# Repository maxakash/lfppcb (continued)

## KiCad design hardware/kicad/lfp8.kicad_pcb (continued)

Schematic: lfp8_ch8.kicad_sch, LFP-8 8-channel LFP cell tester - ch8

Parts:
C801, C802, C806, C808, C811: 10n; C_0603_1608Metric; LCSC C57112
C803, C807: 1u; C_0603_1608Metric; LCSC C15849
C804: 100n; C_0603_1608Metric; LCSC C14663
C805, C810: 47n; C_0603_1608Metric; LCSC C1622
C809: 1n; C_0603_1608Metric; LCSC C1588
D801: SS34; D_SMA; MPN SS34; LCSC C8678
D802, D803, D804, D805, D807, D808, D809, D810: BAT54WS; D_SOD-323; MPN BAT54WS; LCSC C7502694
D806: Green; LED_0805_2012Metric; MPN 0805 green; LCSC C2297
F801: PTC 2A; Fuse_1812_4532Metric; MPN 1812L200/30GR; LCSC C18198342
J801: XH-6P; JST_XH_B6B-XH-A_1x06_P2.50mm_Vertical; MPN JST B6B-XH-A (or clone); JLC Hand
Q801: AO3401A; SOT-23; MPN AO3401A; LCSC C15127
Q802, Q806, Q810, Q811: MMBT3904; SOT-23; MPN MMBT3904; LCSC C20526
Q803: 2N7002; SOT-23; MPN 2N7002; LCSC C8545
Q804, Q805, Q808: AO3400A; SOT-23; MPN AO3400A; LCSC C20917
Q807, Q809: MMBT3906; SOT-23; MPN MMBT3906; LCSC C7420354
R801, R802, R822: 100; R_0603_1608Metric; LCSC C22775
R803, R807, R817, R839: 10k; R_0603_1608Metric; LCSC C25804
R804: 4.7k; R_0603_1608Metric; LCSC C23162
R805, R814, R835, R836, R837, R838, R840: 1k; R_0603_1608Metric; LCSC C21190
R806: 1.2R 2W; R_2512_6332Metric; MPN FRP2512F1R20TS; LCSC C7468247
R808, R809, R810, R811, R812, R818, R823, R832, R844, R848: 100k; R_0603_1608Metric; LCSC C25803
R813: 49.9k; R_0603_1608Metric; LCSC C23184
R815, R834, R841, R851, R852: 47k; R_0603_1608Metric; LCSC C25819
R816: 30k; R_0603_1608Metric; LCSC C22984
R819: 75k; R_0603_1608Metric; LCSC C23242
R820: 36k; R_0603_1608Metric; LCSC C23147
R821, R849: 1M; R_0603_1608Metric; LCSC C22935
R824, R825, R826, R827: 11R 2W; R_2512_6332Metric; MPN FRP2512F11R0TS; LCSC C7468192
R828, R847: 68k; R_0603_1608Metric; LCSC C23231
R829, R842: 33k; R_0603_1608Metric; LCSC C4216
R830: 62k; R_0603_1608Metric; LCSC C23221
R831: 240k; R_0603_1608Metric; LCSC C4197
R833: 150k; R_0603_1608Metric; LCSC C22807
R843: 360k; R_0603_1608Metric; LCSC C23146
R845: 27k; R_0603_1608Metric; LCSC C22967
R846: 200k; R_0603_1608Metric; LCSC C25811
R850: 0.1R 1% 50ppm; R_2512_Kelvin; MPN FRM252WFR100TN; LCSC C7420048
R853: 22k; R_0603_1608Metric; LCSC C31850
R855: 91k; R_0603_1608Metric; LCSC C23265
U801: LM324; SOIC-14_3.9x8.7mm_P1.27mm; MPN LM324DT; LCSC C71035

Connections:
+3V3: R839.1; also elsewhere on the board
+5V: C804.1, C809.2, Q801.2 (S), Q809.2 (E), R803.2, R832.1, R851.1, U801.4 (V+); also elsewhere on the board
/ch8/BNS_8: C802.1, J801.3, R802.1, R836.1, R841.1, R844.1, R847.1
/ch8/BN_8: J801.4, Q805.3 (D), R802.2, R833.1
/ch8/BPF_8: F801.1, J801.1
/ch8/BPS_8: C801.1, J801.2, R801.1, R815.1, R818.1, R828.1, R835.1
/ch8/BP_8: C803.1, F801.2, Q806.2 (E), R801.2, R806.2, R809.1, R824.1, R825.1, R826.1, R827.1, R834.2, R855.2
/ch8/CCN_8: C805.2, R812.2, R813.1, U801.2 (-)
/ch8/CCO_8: D802.1 (K), R814.1, U801.1
/ch8/CCP_8: C810.1, D807.2 (A), R809.2, R810.2, R811.1, U801.3 (+)
/ch8/CCZ_8: C805.1, R814.2
/ch8/CH1_8: D801.2 (A), Q801.3 (D)
/ch8/CH2_8: D801.1 (K), R806.1, R812.1
/ch8/CVO_8: D803.1 (K), R817.1, U801.7
/ch8/CVP_8: C811.1, D808.2 (A), R841.2, R842.2, R843.1, U801.5 (+)
/ch8/CVS_8: C806.2, R815.2, R816.1, U801.6 (-)
/ch8/CVZ_8: C806.1, R817.2
/ch8/DDRV_8: Q803.1 (G), R821.1, R822.1, U801.8
/ch8/DG_8: Q804.1 (G), R822.2, R823.1
/ch8/DLOAD_8: Q804.3 (D), R824.2, R825.2, R826.2, R827.2
/ch8/E2_8: Q802.2 (E), R805.1
/ch8/G1_8: C809.1, Q801.1 (G), Q802.3 (C), R803.1
/ch8/GENB_8: Q810.1 (B), R852.2
/ch8/GEN_8: D804.2 (A), D805.2 (A), D810.1 (K), Q806.3 (C), Q811.3 (C), R832.2, R852.1
/ch8/GISO_8: Q805.1 (G), Q808.1 (G), Q809.3 (C), R853.1
/ch8/GPB_8: Q809.1 (B), Q810.3 (C), R851.2
/ch8/LEDA_8: D806.2 (A), R840.2
/ch8/MIDISO_8: Q805.2 (S), Q808.2 (S), R853.2
/ch8/NBB_8: Q802.1 (B), R804.2
/ch8/NB_8: D802.2 (A), D803.2 (A), D810.2 (A), Q803.3 (D), R804.1, R807.2, R808.1
/ch8/OVO_8: D804.1 (K), R831.1, U801.14
/ch8/OVP_8: R830.2, R831.2, R847.2, R848.1, U801.12 (+)
/ch8/OVS_8: C807.1, D809.2 (A), R828.2, R829.1, U801.13 (-)
/ch8/SHNK_8: R838.1, R850.4
/ch8/SHPK_8: R837.1, R850.3
/ch8/SHP_8: Q808.3 (D), R850.1
/ch8/SNB_8: Q806.1 (B), Q807.2 (E), R833.2, R855.1
/ch8/SNC_8: Q807.3 (C), Q811.1 (B), R849.1
/ch8/SNPB_8: Q807.1 (B), R834.1
/ch8/SUMD_8: R818.2, R819.2, R820.1, R821.2, U801.10 (+)
/ch8/UVN_8: R844.2, R845.2, R846.1, U801.9 (-)
CHGEN_8: D807.1 (K), D808.1 (K), R807.1; also elsewhere on the board
DISEN_8: R819.1; also elsewhere on the board
GND: C801.2, C802.2, C803.2, C804.2, C807.2, C808.2, C810.2, C811.2, D806.1 (K), J801.6, Q803.2 (S), Q804.2 (S), Q810.2 (E), Q811.2 (E), R805.2, R808.2, R811.2, R813.2, R816.2, R820.2, R823.2, R829.2, R843.2, R846.2, R848.2, R849.2, R850.2, U801.11 (V-); also elsewhere on the board
LED_8: R840.1; also elsewhere on the board
MXA_8: R835.2; also elsewhere on the board
MXB_8: R836.2; also elsewhere on the board
MXC_8: R837.2; also elsewhere on the board
MXE_8: R838.2; also elsewhere on the board
NTC_8: C808.1, J801.5, R839.2; also elsewhere on the board
SAFE_EN: D805.1 (K), D809.1 (K); also elsewhere on the board
VREF: R830.1, R842.1, R845.1; also elsewhere on the board
VS: R810.1; also elsewhere on the board

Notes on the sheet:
Cell channel 8: charger, discharger, protection, measurement

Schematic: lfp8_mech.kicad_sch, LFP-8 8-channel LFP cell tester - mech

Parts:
H1, H2, H3, H4: M3; MountingHole_3.2mm_M3; JLC Hand

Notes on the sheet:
Mounting holes

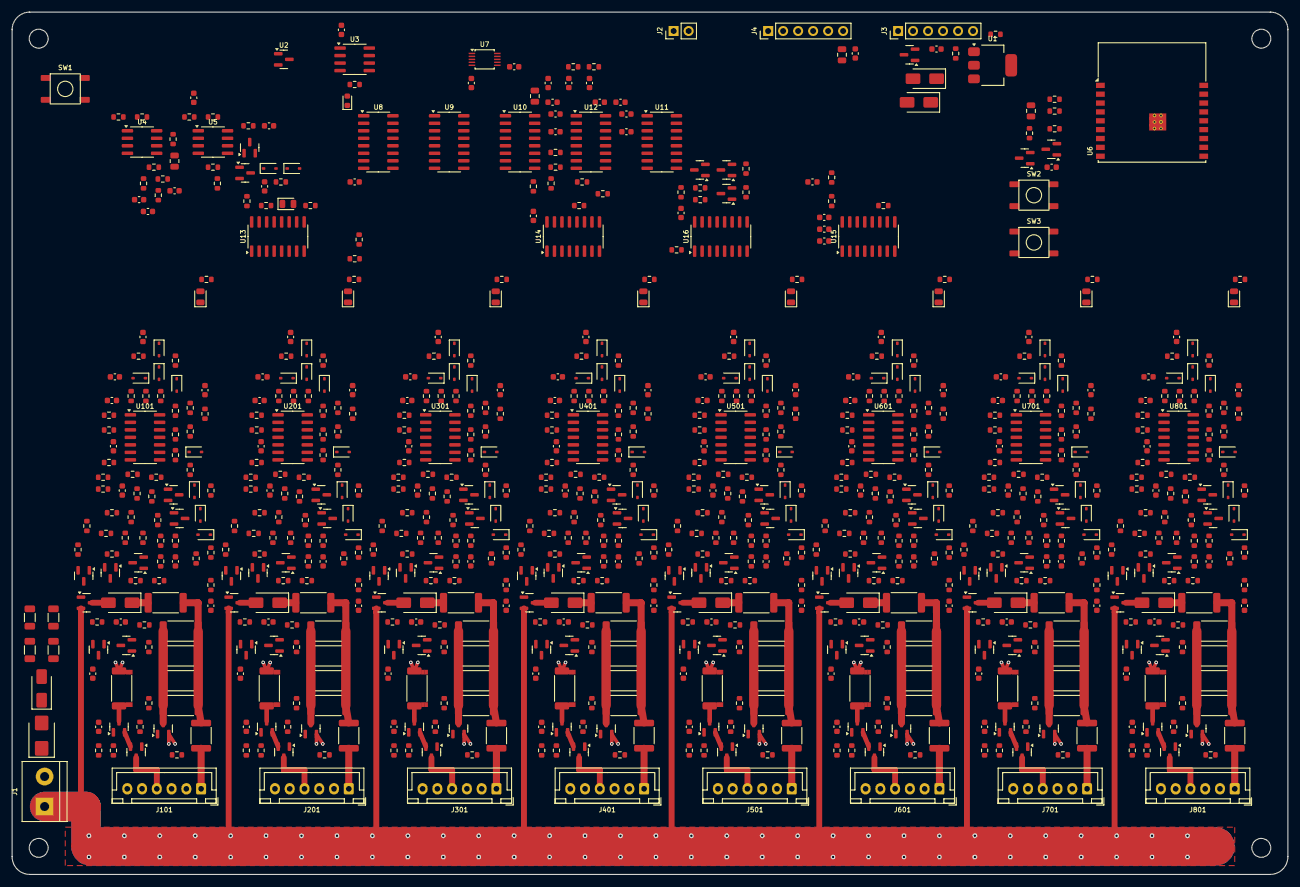
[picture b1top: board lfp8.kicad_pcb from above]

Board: 2 copper layers, 216.0 x 146.0 mm, 835 parts (0 on the bottom side), 431 nets.

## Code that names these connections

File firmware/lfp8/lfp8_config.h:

// LFP-8 firmware - fixed board constants, pin map and timing.
// Source of truth: docs/INTERFACE.md (sections referenced below).
// Pure C++ (no Arduino headers) - shared by the ESP32 build and host tests.
#pragma once
#include <stdint.h>

#define LFP8_FW_VERSION "1.0.0"

namespace lfp8 {

constexpr int kNumCh = 8;  // channels per board

// ---- §8 fixed board constants ---------------------------------------------
constexpr float kRShunt = 0.100f;        // ohm, current shunt
constexpr float kRChgBallast = 1.2f;     // ohm, charge path (also the CC sense resistor)
constexpr float kRLoad = 2.75f;          // ohm, discharge load (4 x 11R)
constexpr float kDivVchk = 0.5f;         // ADC_VCHK = B+S * 0.5
constexpr float kDivVin = 0.3197f;       // ADC_VIN = +5V * 0.3197
constexpr float kNtcPullup = 10000.0f;   // ohm to 3.3 V
constexpr float kNtcR25 = 10000.0f;      // ohm
constexpr float kNtcBeta = 3950.0f;      // K
constexpr float kNtcSupply = 3.3f;       // V
constexpr float kVref = 2.495f;          // V
constexpr float kCvSetNom = 3.576f;      // V, hardware CV (nominal; 3.51..3.62 with tolerances)
constexpr float kOvTrip = 3.82f;         // V, hardware OV latch (3.78..3.87), releases < 2.74 V or SAFE_EN low
constexpr float kOvRelease = 2.74f;
constexpr float kUvTrip = 2.22f;         // V, hardware UV backstop under load (DIS_EN=1)
constexpr float kUvRearm = 2.59f;        // V, the load cannot (re)start below this
constexpr float kDisStartMinV = 2.62f;   // refuse discharge starts below (load would not start)
constexpr float kTbrdSlope = -0.00197f;  // V/K, MMBT3904 Vbe at ~100 uA (§8)
constexpr float kTbrdV25Default = 0.601f;// V at 25 C (§8)

// §4 charge-current DAC: set-point at a 5.20 V rail, scales with V_IN/5.20
constexpr float kIsetLutA[8] = {0.0f, 0.265f, 0.532f, 0.797f, 1.064f, 1.328f, 1.595f, 1.860f};
constexpr float kIsetRefRail = 5.20f;
// §4 passive ceiling of the linear charger: I_max = (V_IN - 0.38 V - V_cell) / 1.5 ohm
constexpr float kChgCeilDrop = 0.38f;
constexpr float kChgCeilR = 1.5f;
constexpr float kRailNominal = 5.20f;   // recommended +5V setting (5.00..5.25 allowed)
constexpr float kRailUvTrip = 4.48f;    // hardware rail UV
constexpr float kRailOvTrip = 5.50f;    // hardware rail OV
// §4 thermal policy of the SOT-23 pass FET
constexpr uint32_t kPulse50PeriodMs = 1000;  // 2.80..3.05 V: 50 % duty, 1 s period
constexpr uint32_t kPre20OnMs = 1000;        // 2.00..2.80 V: 20 % duty (1 s on / 4 s off)
constexpr uint32_t kPre20OffMs = 4000;
constexpr uint8_t kIsetDefault = 4;
constexpr uint8_t kIsetHotLimit = 5;     // ISET >= 6 only when board < 50 C
constexpr float kIsetHotTempC = 50.0f;
constexpr uint8_t kIsetIrPulse = 4;      // §7.1 charge-pulse fallback uses ISET 4

// ---- §2 GPIO map ----------------------------------------------------------
constexpr int kPinAdcNtc = 0;    // IO0  ADC1_CH0 mux D (cell NTC)
constexpr int kPinAdcVchk = 1;   // IO1  ADC1_CH1 mux A / 2
constexpr int kPinRclk = 2;      // IO2  74HC595 latch (strap)
constexpr int kPinAdcVin = 3;    // IO3  +5V * 0.3197
constexpr int kPinAdcTbrd = 4;   // IO4  board temperature (Vbe)
constexpr int kPinSda = 5;       // IO5
constexpr int kPinScl = 6;       // IO6
constexpr int kPinSer = 7;       // IO7  74HC595 serial data
constexpr int kPinSrclk = 8;     // IO8  74HC595 shift clock (strap)
constexpr int kPinBoot = 9;      // IO9  BOOT button, active low
constexpr int kPinHeartbeat = 10;// IO10 watchdog charge pump - software toggled only
constexpr int kPinSafeRb = 20;   // IO20 SAFE_EN read-back
constexpr int kPinFan = 21;      // IO21 fan MOSFET gate
constexpr uint8_t kAdsAddr = 0x48;

// ---- measurement timing ---------------------------------------------------
constexpr uint32_t kMuxSettleUs = 2500;     // >= 2 ms after mux change (§5)
constexpr uint32_t kVchkDwellUs = 26000;    // IO1 divider 1M/1M + 10 nF (tau 5 ms): >= 25 ms on the channel
constexpr uint32_t kSrRefreshMs = 20;       // periodic shift-register refresh
constexpr uint32_t kStaleSampleMs = 3000;   // active channel w/o valid sample -> ADC fault
constexpr uint32_t kSafeGraceMs = 300;      // heartbeat running this long -> SAFE_RB expected
constexpr uint32_t kSafeDebounceMs = 1;     // SAFE_RB low on 2 consecutive reads >= 1 ms apart
// hardware: heartbeat >= 100 Hz (toggle <= 5 ms), trips 23..33 ms after it stops,
// SAFE_EN low ~50 ms after power-up (VREF settling)
constexpr uint32_t kStartupSafeTimeoutMs = 2000;
constexpr uint32_t kOutputSettleMs = 300;   // after outputs off before "stray current" check
constexpr float kStrayCurrentA = 0.10f;
constexpr uint8_t kStrayCount = 3;
constexpr uint8_t kXchkFailCount = 3;       // consecutive cross-check failures -> fault
constexpr uint8_t kI2cFailBoard = 5;        // consecutive I2C failures -> board fault
constexpr float kIAbsMaxA = 2.2f;           // implausible |I| (PTC hold 2 A, charger <= 1.7 A)
constexpr float kVPresentMin = 0.5f;        // §5: below -> EMPTY (with no current)
constexpr float kVReversed = -0.5f;         // below -> REVERSED
constexpr float kIEmptyMax = 0.05f;
constexpr float kXchkMinCellV = 1.0f;       // cross-check only when a cell is present
// B- diagnostic (§5, AIN1-AIN3 = I * (R_bminus + 2 x 28 mOhm MOSFETs + 0.1 ohm shunt))
constexpr float kRbmFixed = 0.156f;         // ohm: MOSFETs + shunt
constexpr float kContactWarnOhm = 0.30f;    // implied B- force-path resistance -> CONTACT_WARN
constexpr float kContactMinI = 0.20f;       // A, needed for a meaningful estimate
// OV latch (§6)
constexpr float kOvLatchDetectV = 3.75f;    // CHG_EN=1, I ~ 0 and V >= this -> latch tripped
constexpr uint32_t kLatchResetMs = 120;     // heartbeat stop to release all latches (>= 100 ms)

// ---- IR (§7.1) ------------------------------------------------------------
constexpr int kIrBaseSamples = 16;          // V0/I0 average
constexpr float kIrTOhmic = 0.010f;         // s
constexpr float kIrTDc = 1.000f;            // s
constexpr float kIrPulseEnd = 1.012f;       // s, keep pulse until both V and I bracket 1 s
constexpr float kIrUvBlock = 2.65f;         // below: discharge pulse blocked by UV backstop
constexpr float kIrMinDeltaI = 0.30f;       // |I(t)-I0| below this -> pulse failed
constexpr uint32_t kIrMaxDurationMs = 2500; // engine watchdog
constexpr int kIrMaxSamples = 1100;

// ---- networking (§9) --------------------------------------------------------
constexpr uint16_t kHelloPort = 45454;
constexpr uint32_t kHelloPeriodMs = 2000;
constexpr uint32_t kPeerTimeoutMs = 10000;
constexpr int kMaxPeers = 16;

// ---- history ring -----------------------------------------------------------
constexpr uint32_t kHistIntervalMs = 30000;  // 1 sample / 30 s
constexpr int kHistLen = 2880;               // 24 h per channel

}  // namespace lfp8
